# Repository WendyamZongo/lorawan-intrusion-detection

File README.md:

# 🚨 LoRaWAN PIR Motion Detection System

A complete IoT security system for real-time motion detection using LoRaWAN technology, designed for African livestock farm security.

## 📋 Overview

This system detects :
- **Motion** via AM312 PIR sensor
- **Instant alerts** via LoRaWAN EU868
- **Web dashboard** with sound alarm
- **Multiple locations** support

---

## 🏗️ System Architecture

```
ATmega328P Node (Security Node)
├── AM312 PIR Sensor
└── RFM95W LoRa Radio (EU868)
        │
        │ LoRaWAN ABP
        ▼
RAK5146 Gateway (Raspberry Pi 4B)
        │
        ▼
ChirpStack v4 Network Server
        │
        └── PIR Security Dashboard (port 5001)
```

---

## 🛠️ Hardware

| Component | Specification |
|-----------|--------------|
| MCU | ATmega328P-P (DIP-28) |
| LoRa Radio | RFM95W 868MHz |
| PIR Sensor | AM312 (3.3V) |

---

## 📌 Pin Configuration

```
AM312 PIR    ATmega328P
─────────    ──────────
VCC      →   3.3V
GND      →   GND
OUT      →   D3 (interrupt pin)

RFM95W     ATmega328P
───────    ──────────
VCC    →   3.3V
GND    →   GND
SCK    →   D13
MISO   →   D12
MOSI   →   D11
NSS    →   D10
RST    →   D9
DIO0   →   D2
```

---

## 🚀 Quick Start

### 1. Gateway Setup
```bash
cd ~/chirpstack-docker
docker compose up -d
cd ~/sx1302_hal/packet_forwarder
sudo ./lora_pkt_fwd
```

### 2. Dashboard Setup
```bash
pip install flask paho-mqtt --break-system-packages
nohup python3 webapp/app.py > /dev/null 2>&1 &
```

### 3. ChirpStack Setup
- Create device profile : `ATmega-EU868-PIR` (ABP, no OTAA)
- Add decoder from `chirpstack/decoders/pir_decoder.js`
- Register device and get ABP keys
- Update firmware with new keys

---

## 🌐 Dashboard

| URL | Description |
|-----|-------------|
| http://yam.local:5001 | PIR Motion Dashboard |

### Features :
- 🚨 **Real-time motion alerts** with blinking red screen
- 🔔 **Sound alarm** when motion detected
- 🔕 **Stop Alert** button to silence alarm
- 📍 **Location tagging** per sensor
- 📊 **Event history** (last 20 events)
- 📡 **RSSI signal strength** display

---

## 📡 LoRaWAN Configuration

| Parameter | Value |
|-----------|-------|
| Region | EU868 |
| Activation | ABP |
| Spreading Factor | SF7 |
| Bandwidth | 125 kHz |
| Sync Word | 0x34 |
| Payload | 1 byte (0x01=DETECTED) |

---

## 🗂️ Repository Structure

```
pir-monitoring/
├── README.md
├── firmware/
│   └── atmega328p/
│       └── Intrusion.ino              # ATmega328P firmware
├── chirpstack/
│   └── Intrusion_decoder.js            # ChirpStack decoder
├── hardware/
│   └── Intrusion.kicad_pcb
|   └── Intrusion.kicad_pro
|   └── Intrusion.kicad_sch
├── webapp/
│   └── app.py                        # PIR motion dashboard
└── scripts/
    └── start_all.sh                  # Auto-start script
```

---

## 📍 Adding Locations

Edit `webapp/app.py` :
```python
DEVICE_LOCATIONS = {
    "PIR-node-1": "Main Gate JKUAT",
    "PIR-node-2": "Back Gate",
    "PIR-node-3": "Field A",
}
```

---

## 📄 License

MIT License — Free to use for educational and commercial purposes.

---

## 👨‍💻 Author

Wendyam Clovis Dubois Zongo MSc Electrical Engineering (Computer Engineering), PAUSTI / JKUAT, Nairobi Embedded systems and FPGA engineer

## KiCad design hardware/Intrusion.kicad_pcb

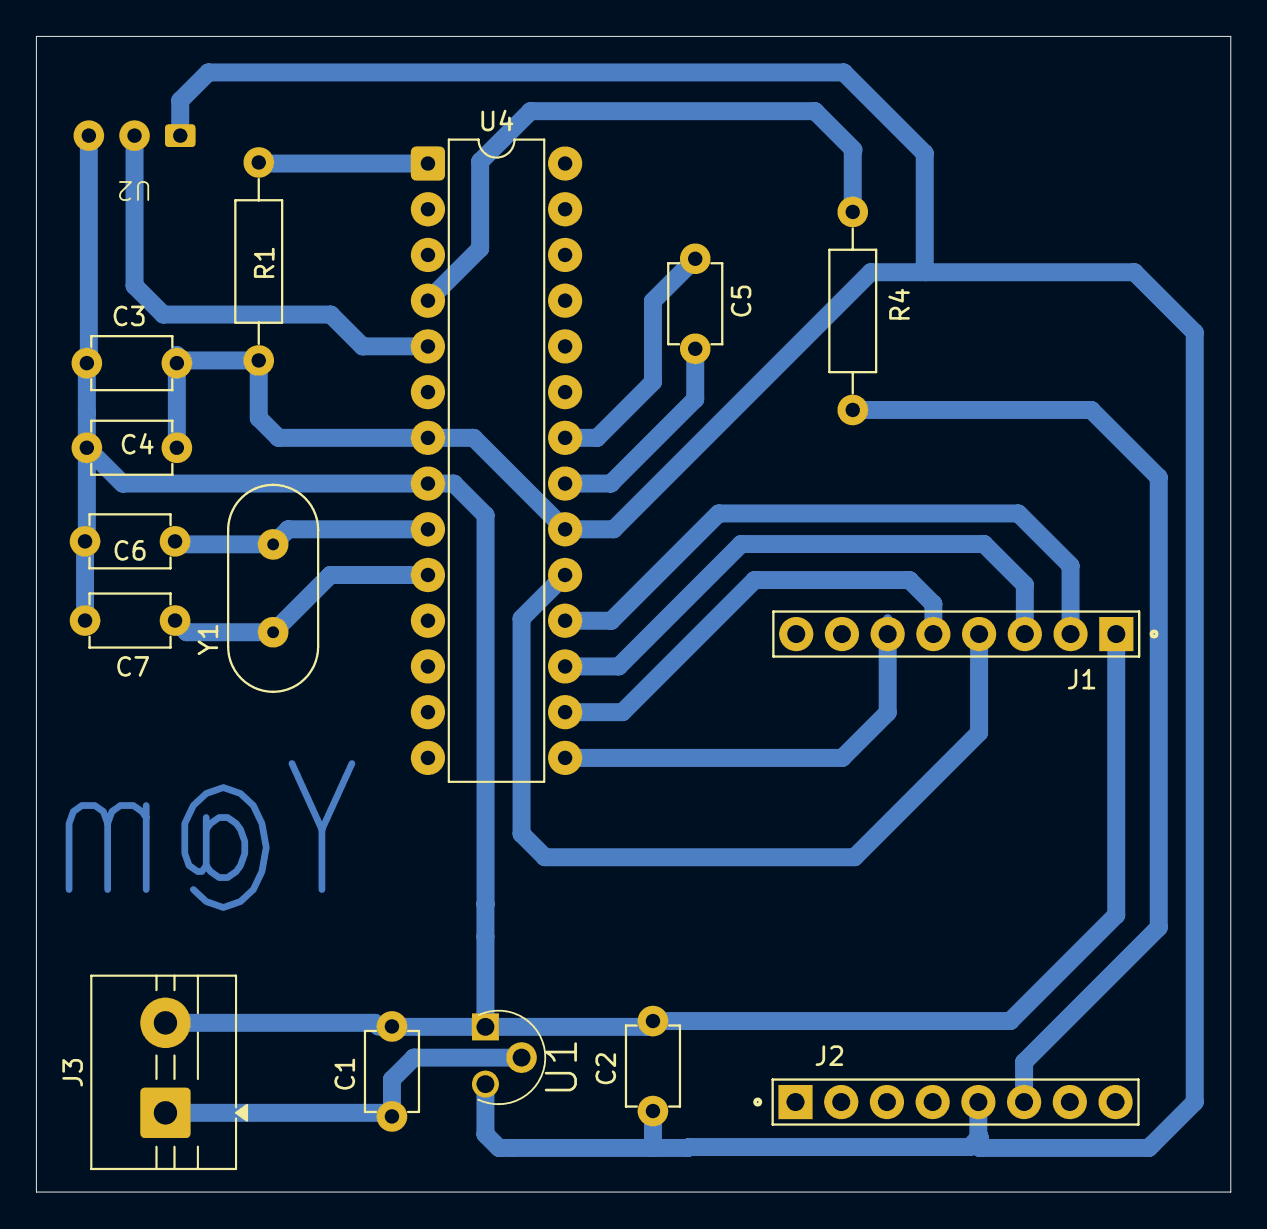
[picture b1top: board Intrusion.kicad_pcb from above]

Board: 2 copper layers, 66.3 x 64.2 mm, 16 parts (0 on the bottom side), 15 nets.

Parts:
C1, C2: 1 uF; CAPRB500W50L450T300H550
C3, C4, C5: 100 nF; CAPRB500W50L450T300H550
C6, C7: 22 pF; CAPRB500W50L450T300H550
J1, J2: 1986717-8; TE_826629-8
J3: Screw_Terminal_01x02; TerminalBlock_MaiXu_MX126-5.0-02P_1x02_P5.00mm
R1: 10 K; RESAD1100W55L680D260
R4: 0; RESAD1100W55L680D260
U1: MCP1700-3302E_TO; TO127P254X495-3
U2: AM312-PIR
U4: ATmega328P-P; DIP-28_W7.62mm
Y1: 8 MHz; XTAL_HC49P488W46L1150T500H350

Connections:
3.7V: C1.1, J3.1, U1.2 (VIN)
+3.3V: C2.1, C3.2, C4.2, J2.5, R1.2, U1.3 (VOUT), U2.1 (Vdd), U4.7 (VCC), U4.20 (AVCC)
/DI0: J2.6, R4.2
/MISO: J1.2, U4.18 (PB4)
/MOSI: J1.3, U4.17 (PB3)
/NSS: J1.5, U4.16 (PB2)
/RST: J1.6, U4.15 (PB1)
/SCK: J1.4, U4.19 (PB5)
/Vo: U2.2 (Vo), U4.5 (PD3)
GND: C1.2, C2.2, C3.1, C4.1, C5.1, C6.2, C7.2, J1.1, J3.2, U1.1 (GND), U2.3 (Gnd), U4.8 (GND), U4.22 (GND)
unnamed: C5.2, U4.21 (AREF)
unnamed: R4.1, U4.4 (PD2)
unnamed: C6.1, U4.9 (XTAL1/PB6), Y1.2
unnamed: C7.1, U4.10 (XTAL2/PB7), Y1.1
unnamed: R1.1, U4.1 (~RESET/PC6)
